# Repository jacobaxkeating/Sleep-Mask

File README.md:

# Circadian Sleep Mask

## Overview
A battery powered sleep mask that gradually illuminates the inside of the mask as the user's alarm approaches. The user sets their sleep duration by pressing a button on the housing, and the device begins lighting up that many hours later. Waking this way is closer to how the body wakes naturally, easing the user out of sleep rather than jolting them awake. It reduces sleep inertia, the grogginess and disorientation that follows an abrupt alarm

[Schematic (PDF)](outputs/schematic/sleep_mask.pdf)

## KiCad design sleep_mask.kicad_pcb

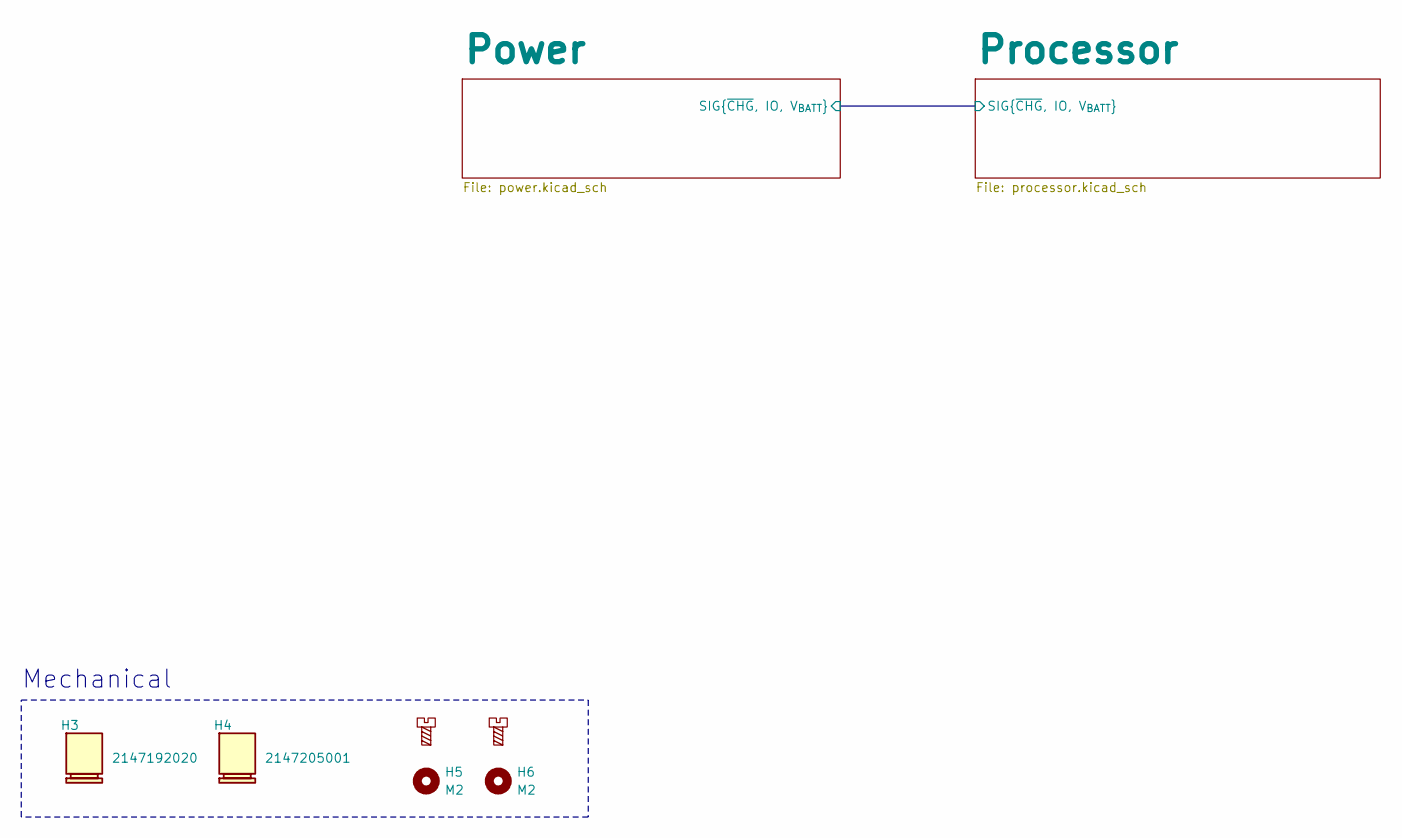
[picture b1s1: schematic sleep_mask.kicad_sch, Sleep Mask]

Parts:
H1, H2: MountingScrew
H3: 2147192020; Manufacturer_Part_Number 2147192020
H4: 2147205001; Manufacturer_Part_Number 2147205001
H5, H6: M2; MountingHole_2.2mm_M2

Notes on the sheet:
Mechanical

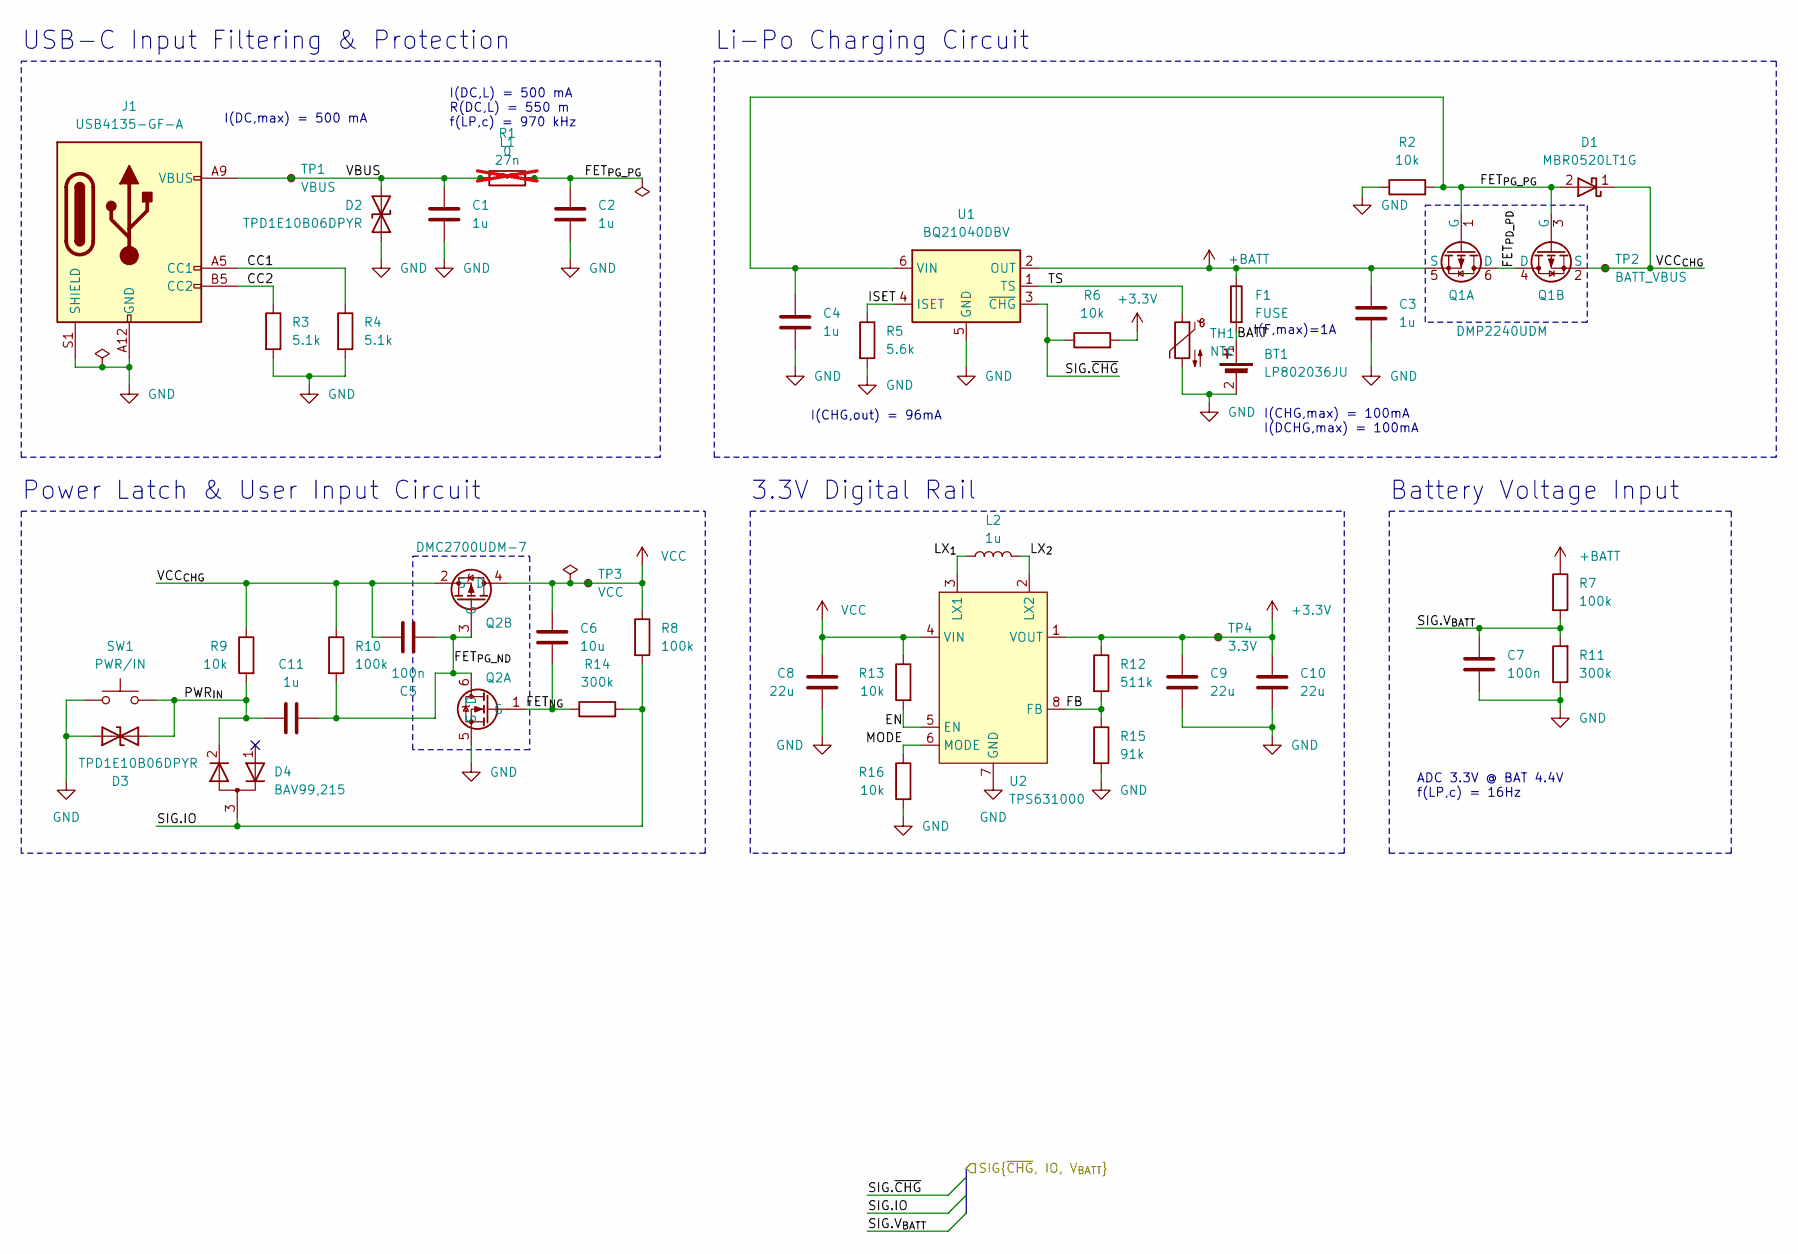
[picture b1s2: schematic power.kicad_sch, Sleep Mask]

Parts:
BT1: LP802036JU; R_1206_3216Metric_Pad1.30x1.75mm_HandSolder; Manufacturer_Part_Number LP802036JU +PCM+2IC+2 WIRES 50MM
C1, C2, C3, C4, C11: 1u; C_0402_1005Metric; Manufacturer_Part_Number CL05A105KO5NNNC
C5, C7: 100n; C_0402_1005Metric; Manufacturer_Part_Number CL05B104KO5NNNC
C6: 10u; C_0603_1608Metric; Manufacturer_Part_Number CL10X106MO8NRNC
C8, C9, C10: 22u; C_0805_2012Metric; Manufacturer_Part_Number CL21A226MAYNNNE
D1: MBR0520LT1G; D_SOD-123; Manufacturer_Part_Number MBR0520LT1G
D2, D3: TPD1E10B06DPYR; Texas_DPY0002A_0.6x1mm_P0.65mm; Manufacturer_Part_Number TPD1E10B06DPYR
D4: BAV99,215; TSOT-23; Manufacturer_Part_Number BAV99,215
F1: FUSE; R_0603_1608Metric; Manufacturer_Part_Number MFU0603FF01000P500
J1: USB4135-GF-A; USB_C_Receptacle_GCT_USB4135-GF-A_6P_TopMnt_Horizontal; Manufacturer_Part_Number USB4135-GF-A
L1: 27n; L_0603_1608Metric; Manufacturer_Part_Number LQG18HN27NJ00D; not fitted
L2: 1u; L_0603_1608Metric; Manufacturer_Part_Number DFE18SAN1R0MG0L
Q1: DMP2240UDM; SOT-23-6; Manufacturer_Part_Number DMP2240UDM
Q2: DMC2700UDM-7; SOT-23-6; Manufacturer_Part_Number DMC2700UDM-7
R1: 0; R_0603_1608Metric; Manufacturer_Part_Number RC0603JR-070RL
R2, R6, R9, R13, R16: 10k; R_0603_1608Metric; Manufacturer_Part_Number RK73H1JTTD1002F
R3, R4: 5.1k; R_0603_1608Metric; Manufacturer_Part_Number RK73H1JTTD5101F
R5: 5.6k; R_0603_1608Metric; Manufacturer_Part_Number RC0603FR-075K6L
R7, R8, R10: 100k; R_0603_1608Metric; Manufacturer_Part_Number RK73H1JTTD1003F
R11, R14: 300k; R_0603_1608Metric; Manufacturer_Part_Number RK73H1JTTD3003F
R12: 511k; R_0603_1608Metric; Manufacturer_Part_Number RK73H1JTTD5113F
R15: 91k; R_0603_1608Metric; Manufacturer_Part_Number RC0603FR-0791KL
SW1: PWR/IN; SW_Push_1P1T-MP_NO_Horizontal_Alps_SKRTLAE010; Manufacturer_Part_Number SKRTLAE010
TH1: NTC; R_0402_1005Metric; Manufacturer_Part_Number NTCG103JF103FT1
TP1: VBUS; TestPoint_Pad_D1.0mm
TP2: BATT_VBUS; TestPoint_Pad_D1.0mm
TP3: VCC; TestPoint_Pad_D1.0mm
TP4: 3.3V; TestPoint_Pad_D1.0mm
U1: BQ21040DBV; SOT-23-6; Manufacturer_Part_Number BQ21040DBVT
U2: TPS631000; SOT-583-8; Manufacturer_Part_Number TPS631000DRLR

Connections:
+3.3V: C9.2, C10.2, R6.2, R12.1, TP4.1, U2.1 (VOUT); also elsewhere on the board
+BATT: C3.1, F1.1, Q1.5 (S), R7.1, U1.2 (OUT)
/Power/BATT: BT1.1 (+), F1.2
/Power/CC1: J1.A5 (CC1), R4.1
/Power/CC2: J1.B5 (CC2), R3.1
/Power/EN: R13.2, U2.5 (EN)
/Power/FB: R12.2, R15.1, U2.8 (FB)
/Power/FET_{NG}: C6.2, Q2.1 (G), R14.1
/Power/FET_{PD_PD}: Q1.4 (D), Q1.6 (D)
/Power/FET_{PG_ND}: C5.2, C11.2, Q2.3 (G), Q2.6 (D), R10.2
/Power/FET_{PG_PG}: C2.1, C4.1, D1.2 (A), L1.2, Q1.1 (G), Q1.3 (G), R1.2, R2.2, U1.6 (VIN)
/Power/ISET: R5.1, U1.4 (ISET)
/Power/LX_{1}: L2.1, U2.3 (LX1)
/Power/LX_{2}: L2.2, U2.2 (LX2)
/Power/MODE: R16.1, U2.6 (MODE)
/Power/PWR_{IN}: C11.1, D3.2 (A2), D4.2 (K), R9.2, SW1.2
/Power/SIG.IO: D4.3 (common), R8.2, R14.2; also elsewhere on the board
/Power/SIG.V_{BATT}: C7.1, R7.2, R11.2; also elsewhere on the board
/Power/SIG.~CHG: R6.1, U1.3 (~CHG); also elsewhere on the board
/Power/TS: TH1.1, U1.1 (TS)
/Power/VBUS: C1.1, D2.2 (A2), J1.A9 (VBUS), J1.B9 (VBUS), L1.1, R1.1, TP1.1
/Power/VCC_{CHG}: C5.1, D1.1 (K), Q1.2 (S), Q2.2 (S), R9.1, R10.1, TP2.1
GND: BT1.2 (-), C1.2, C2.2, C3.2, C4.2, C7.2, C8.1, C9.1, C10.1, D2.1 (A1), D3.1 (A1), J1.A12 (GND), J1.B12 (GND), J1.S1 (SHIELD), Q2.5 (S), R2.1, R3.2, R4.2, R5.2, R11.1, R15.2, R16.2, SW1.1, TH1.2, U1.5 (GND), U2.7 (GND); also elsewhere on the board
VCC: C6.1, C8.2, Q2.4 (D), R8.1, R13.1, TP3.1, U2.4 (VIN); also elsewhere on the board

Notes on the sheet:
I(F,max)=1A
I(CHG,out) = 96mA
I(DC,max) = 500 mA
I(DC,L) = 500 mA R(DC,L) = 550 m f(LP,c) = 970 kHz
I(CHG,max) = 100mA I(DCHG,max) = 100mA
3.3V Digital Rail
Li-Po Charging Circuit
USB-C Input Filtering & Protection
Battery Voltage Input
Power Latch & User Input Circuit
ADC 3.3V @ BAT 4.4V f(LP,c) = 16Hz

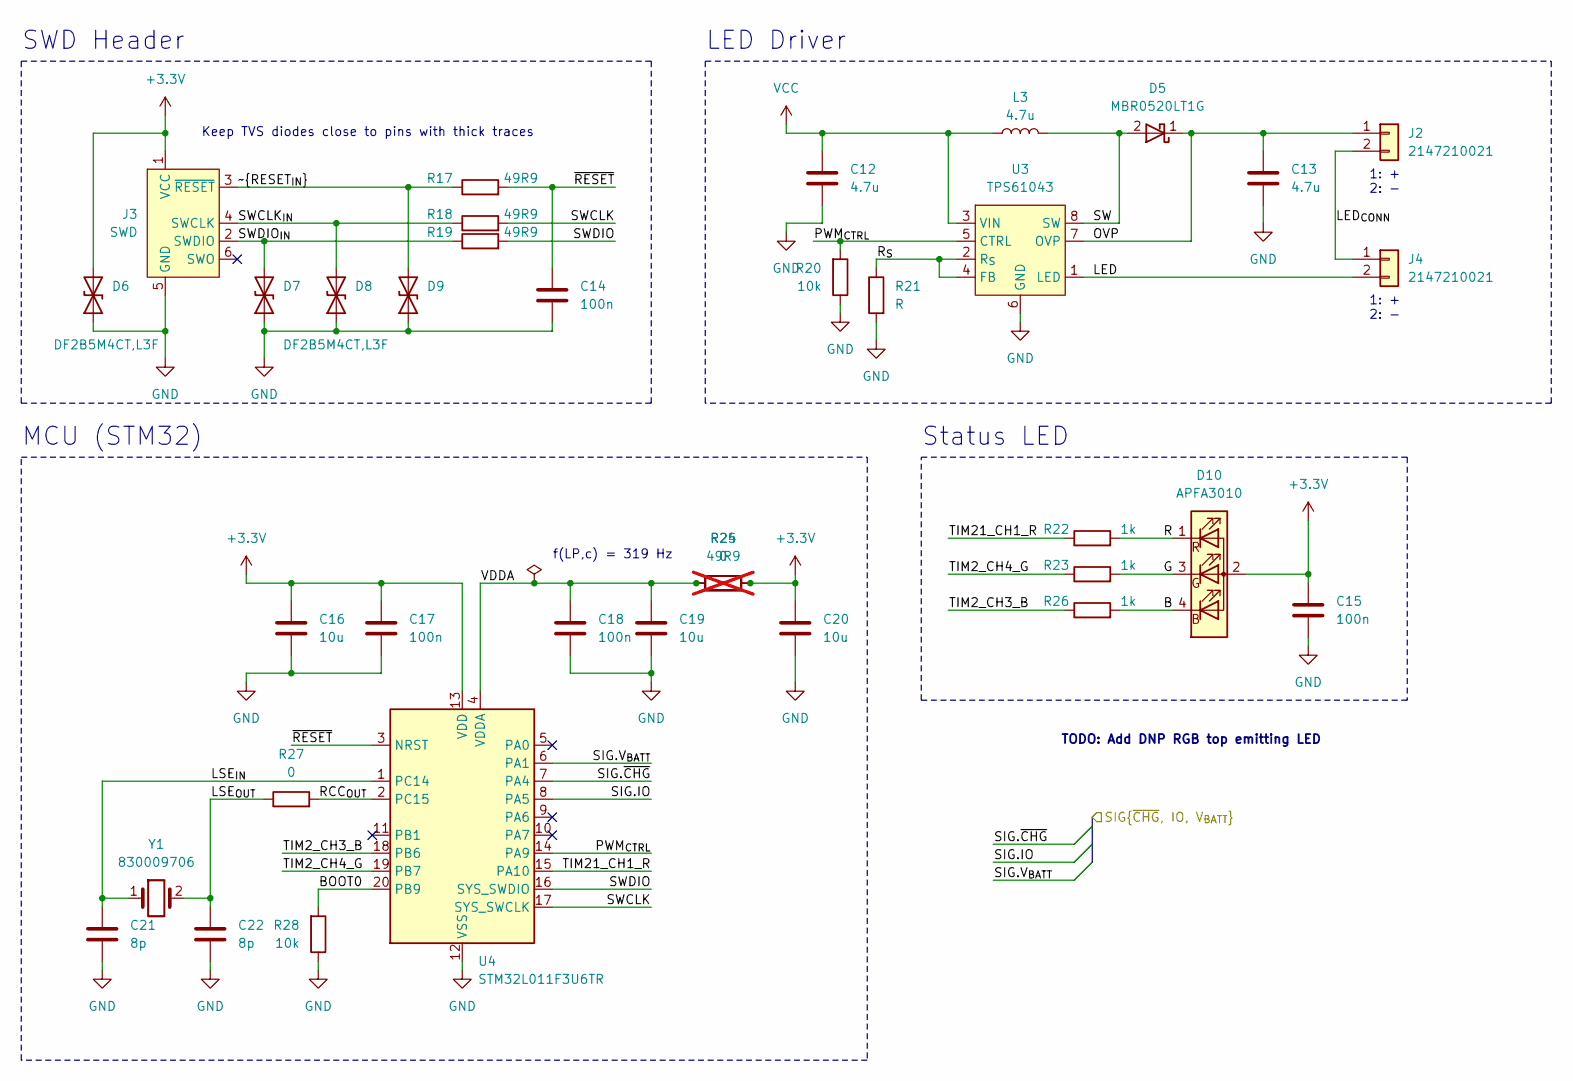
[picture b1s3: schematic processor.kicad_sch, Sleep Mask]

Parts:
C12, C13: 4.7u; C_0603_1608Metric; Manufacturer_Part_Number GRM188R6YA475KE15D
C14, C15, C17, C18: 100n; C_0402_1005Metric; Manufacturer_Part_Number CL05B104KO5NNNC
C16, C19, C20: 10u; C_0603_1608Metric; Manufacturer_Part_Number CL10X106MO8NRNC
C21, C22: 8p; C_0402_1005Metric; Manufacturer_Part_Number CL05C080DB51PNC
D5: MBR0520LT1G; D_SOD-123; Manufacturer_Part_Number MBR0520LT1G
D6, D7, D8, D9: DF2B5M4CT,L3F; D_SOD-882; Manufacturer_Part_Number DF2B5M4CT,L3F
D10: APFA3010; LED_Kingbright_APFA3010_3x1.5mm_Horizontal; Manufacturer_Part_Number APFA3010LSEEZGKQBKC
J2, J4: 2147210021; Manufacturer_Part_Number 2147210021
J3: SWD; Tag-Connect_TC2030-IDC-NL_2x03_P1.27mm_Vertical
L3: 4.7u; L_0805_2012Metric; Manufacturer_Part_Number MLZ2012N4R7LT000
R17, R18, R19: 49R9; R_0603_1608Metric; Manufacturer_Part_Number RC0603FR-0749R9L
R20, R28: 10k; R_0603_1608Metric; Manufacturer_Part_Number RK73H1JTTD1002F
R21: R; R_0603_1608Metric
R22, R23, R26: 1k; R_0603_1608Metric; Manufacturer_Part_Number RK73H1JTTD1001F
R24: 49R9; R_0603_1608Metric; Manufacturer_Part_Number RC0603FR-0749R9L; not fitted
R25, R27: 0; R_0603_1608Metric; Manufacturer_Part_Number RC0603JR-070RL
U3: TPS61043; Texas_DRB0008A; Manufacturer_Part_Number TPS61043DRBR
U4: STM32L011F3U6TR; ST_UFQFPN-20_3x3mm_P0.5mm; Manufacturer_Part_Number STM32L011F3U6TR
Y1: 830009706; Crystal_SMD_G8-2Pin_3.2x1.5mm; MPN ABS05-32.768KHZ-9-T

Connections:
+3.3V: C15.2, C16.1, C17.1, C20.1, D6.2 (A2), D10.2 (A), J3.1 (VCC), R24.2, R25.2, U4.13 (VDD); also elsewhere on the board
/Power/SIG.IO: U4.8 (PA5); also elsewhere on the board
/Power/SIG.V_{BATT}: U4.6 (PA1); also elsewhere on the board
/Power/SIG.~CHG: U4.7 (PA4); also elsewhere on the board
/Processor/B: D10.4 (B), R26.2
/Processor/BOOT0: R28.2, U4.20 (PB9)
/Processor/G: D10.3 (G), R23.2
/Processor/LED: J4.2, U3.1 (LED)
/Processor/LED_{CONN}: J2.2, J4.1
/Processor/LSE_{IN}: C21.1, U4.1 (PC14), Y1.1
/Processor/LSE_{OUT}: C22.1, R27.1, Y1.2
/Processor/OVP: C13.2, D5.1 (K), J2.1, U3.7 (OVP)
/Processor/PWM_{CTRL}: R20.2, U3.5 (CTRL), U4.14 (PA9)
/Processor/R: D10.1 (R), R22.2
/Processor/RCC_{OUT}: R27.2, U4.2 (PC15)
/Processor/R_{S}: R21.1, U3.2 (R_{S}), U3.4 (FB)
/Processor/SW: D5.2 (A), L3.2, U3.8 (SW)
/Processor/SWCLK: R18.2, U4.17 (SYS_SWCLK)
/Processor/SWCLK_{IN}: D8.2 (A2), J3.4 (SWCLK), R18.1
/Processor/SWDIO: R19.2, U4.16 (SYS_SWDIO)
/Processor/SWDIO_{IN}: D7.2 (A2), J3.2 (SWDIO), R19.1
/Processor/TIM2_CH3_B: R26.1, U4.18 (PB6)
/Processor/TIM2_CH4_G: R23.1, U4.19 (PB7)
/Processor/TIM21_CH1_R: R22.1, U4.15 (PA10)
/Processor/VDDA: C18.1, C19.1, R24.1, R25.1, U4.4 (VDDA)
/Processor/~RESET_{IN}: D9.2 (A2), J3.3 (~RESET), R17.1
/Processor/~RESET: C14.2, R17.2, U4.3 (NRST)
GND: C12.1, C13.1, C14.1, C15.1, C16.2, C17.2, C18.2, C19.2, C20.2, C21.2, C22.2, D6.1 (A1), D7.1 (A1), D8.1 (A1), D9.1 (A1), J3.5 (GND), R20.1, R21.2, R28.1, U3.6 (GND), U3.9 (TP), U4.12 (VSS); also elsewhere on the board
VCC: C12.2, L3.1, U3.3 (VIN); also elsewhere on the board

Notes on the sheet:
Keep TVS diodes close to pins with thick traces
SWD Header
TODO: Add DNP RGB top emitting LED
1: + 2: -
LED Driver
f(LP,c) = 319 Hz
MCU (STM32)
Status LED

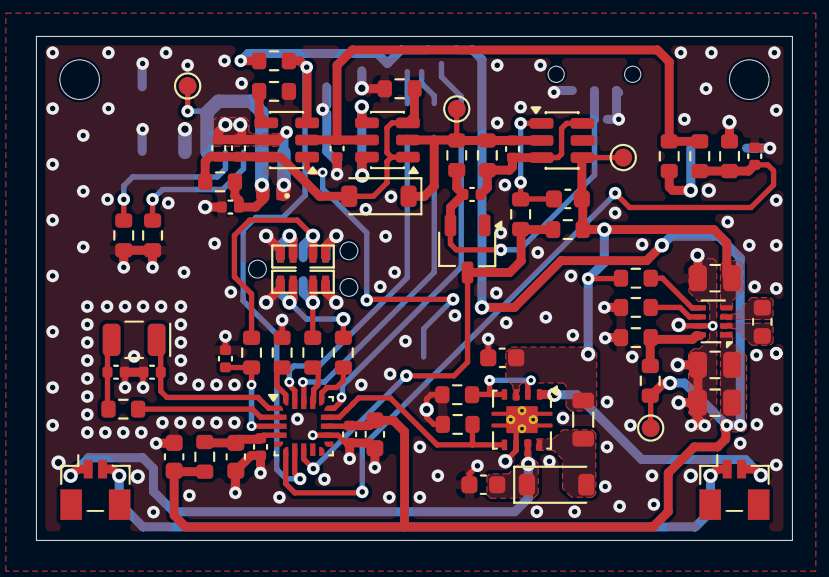
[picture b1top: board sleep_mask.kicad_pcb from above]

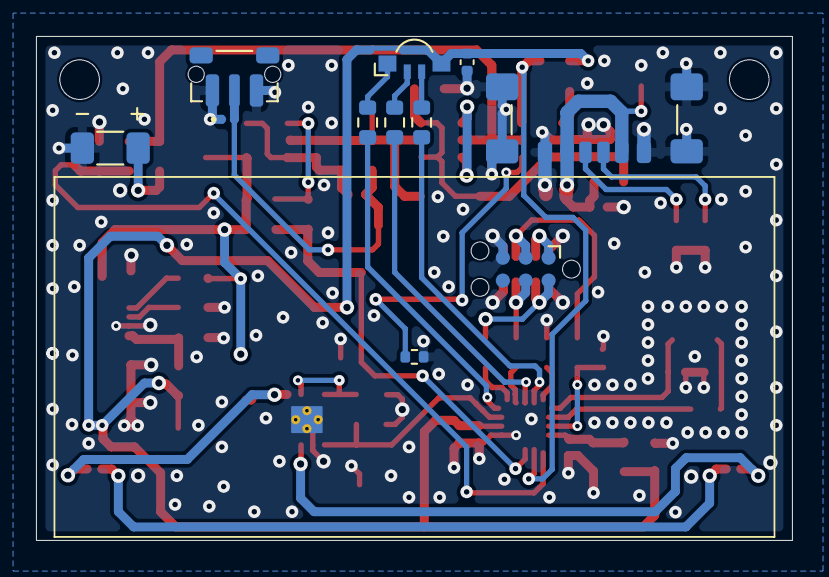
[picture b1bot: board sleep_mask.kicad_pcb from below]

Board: 4 copper layers, 42.0 x 28.0 mm, 82 parts (11 on the bottom side), 47 nets.

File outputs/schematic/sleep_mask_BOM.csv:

"Reference","Value","Qty","MPN1","Manufacturer1","Footprint","Datasheet","COO","DNP","Description","MPN2","Manufacturer2"
"BT1","LP802036JU","1","","","Resistor_SMD:R_1206_3216Metric_Pad1.30x1.75mm_HandSolder","https://www.jauch.com/downloadfile/5ef1edcfd8b3ac6cf0afebf9d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","","","BATTERY 3.7V 500MAH","",""
"C1,C2,C3,C4,C11,L2","1u","6","","","Capacitor_SMD:C_0402_1005Metric,Inductor_SMD:L_0603_1608Metric","https://mm.digikey.com/Volume0/opasdata/d220001/medias/docus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,https://search.murata.co.jp/Ceramy/image/img/P02/JETE243A-0036.pdf","","","CAP CER 1UF 16V X5R 0402,FIXED IND 1UH 1.7A 128 MOHM SMD","",""
"C5,C7,C14,C15,C17,C18","100n","6","","","Capacitor_SMD:C_0402_1005Metric","https://mm.digikey.com/Volume0/opasdata/d220001/medias/docus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","","","CAP CER 0.1UF 16V X7R 0402","",""
"C6,C16,C19,C20","10u","4","","","Capacitor_SMD:C_0603_1608Metric","https://mm.digikey.com/Volume0/opasdata/d220001/medias/docus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","","","CAP CER 10UF 16V X6S 0603","",""
"C8,C9,C10","22u","3","","","Capacitor_SMD:C_0805_2012Metric","https://mm.digikey.com/Volume0/opasdata/d220001/medias/docus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","","","CAP CER 22UF 25V X5R 0805","",""
"C12,C13,L3","4.7u","3","","","Capacitor_SMD:C_0603_1608Metric,Inductor_SMD:L_0805_2012Metric","https://product.tdk.com/en/system/files?file=dam/doc/product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,https://search.murata.co.jp/Ceramy/image/img/A01X/G101/ENG/G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","","","CAP CER 4.7UF 35V X5R 0603,FIXED IND 4.7UH 600MA 180 MOHM","",""
"C21,C22","8p","2","","","Capacitor_SMD:C_0402_1005Metric","https://mm.digikey.com/Volume0/opasdata/d220001/medias/docus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","","","CAP CER 8PF 50V C0G/NP0 0402","",""
"D1,D5","MBR0520LT1G","2","","","Diode_SMD:D_SOD-123","https://www.onsemi.com/pdf/datasheet/mbr0520lt1-d.pdf","","","DIODE SCHOTTKY 20V 500MA SOD123","",""
"D2,D3","TPD1E10B06DPYR","2","","","Package_SON:Texas_DPY0002A_0.6x1mm_P0.65mm","https://www.ti.com/general/docs/suppproductinfo.tsp?distId=1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","","","TVS DIODE 5.5VWM 14VC 2X1SON","",""
"D4","BAV99,215","1","","","Package_TO_SOT_SMD:TSOT-23","https://assets.nexperia.com/documents/data-sheet/BAV99.pdf","","","DIODE ARR GP 100V 215MA TO-236AB","",""
"D6,D7,D8,D9","DF2B5M4CT,L3F","4","","","Diode_SMD:D_SOD-882","https://toshiba.semicon-storage.com/info/docget.jsp?did=5577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","","","TVS DIODE 3.6VWM 15VC CST2","",""
"D10","APFA3010","1","","","LED_SMD:LED_Kingbright_APFA3010_3x1.5mm_Horizontal","https://www.KingbrightUSA.com/images/catalog/SPEC/APFA3010LS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","","","LED RGB CLEAR 4SMD R/A","",""
"F1","FUSE","1","","","Resistor_SMD:R_0603_1608Metric","https://www.vishay.com/docs/28747/mfuserie.pdf","","","FUSE BOARD MOUNT 1A 32VDC 0603","",""
"H3","2147192020","1","","","","https://www.molex.com/en-us/products/part-detail/2147192020?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","","","CONN HDR HSG 2POS 0.80MM","",""
"H4","2147205001","1","","","","https://www.molex.com/pdm_docs/sd/2147205001_sd.pdf","","","ZERO-HACHI 0.8 CRIMP TERM #30-32","",""
"J1","USB4135-GF-A","1","","","Connector_USB:USB_C_Receptacle_GCT_USB4135-GF-A_6P_TopMnt_Horizontal","https://gct.co/files/specs/usb4135-spec.pdf","","","USB C REC GF RA 6P SMT & SMT SHE","",""
"J2,J4","2147210021","2","","","sleep_mask:2147210021","https://www.molex.com/en-us/products/part-detail/2147210021?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","","","ZERO-HACHI 0.8 HDR SR RA ETP AU","",""
"L1","27n","1","","","Inductor_SMD:L_0603_1608Metric","https://search.murata.co.jp/Ceramy/image/img/P02/JELF243B-0002.pdf","","DNP","FIXED IND 27NH 500MA 550 MOHM","",""
"Q1","DMP2240UDM","1","","","Package_TO_SOT_SMD:SOT-23-6","https://www.diodes.com/assets/Datasheets/ds31197.pdf","","","MOSFET 2P-CH 20V 2A SOT26","",""
"Q2","DMC2700UDM-7","1","","","Package_TO_SOT_SMD:SOT-23-6","https://www.diodes.com/assets/Datasheets/DMC2700UDM.pdf","","","MOSFET N/P-CH 20V 1.34A SOT26","",""
"R1,R25,R27","0","3","","","Resistor_SMD:R_0603_1608Metric","https://yageogroup.com/content/datasheet/asset/file/PYU-RC_G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","","","RES 0 OHM JUMPER 1/10W 0603","",""
"R2,R6,R9,R13,R16,R20,R28","10k","7","","","Resistor_SMD:R_0603_1608Metric","https://www.koaspeer.com/pdfs/RK73H.pdf","","","RES 10K OHM 1% 1/10W 0603","",""
"R3,R4","5.1k","2","","","Resistor_SMD:R_0603_1608Metric","https://www.koaspeer.com/pdfs/RK73H.pdf","","","RES 5.1K OHM 1% 1/10W 0603","",""
"R5","5.6k","1","","","Resistor_SMD:R_0603_1608Metric","https://yageogroup.com/content/datasheet/asset/file/PYU-RC_G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","","","RES 5.6K OHM 1% 1/10W 0603","",""
"R7,R8,R10","100k","3","","","Resistor_SMD:R_0603_1608Metric","https://www.koaspeer.com/pdfs/RK73H.pdf","","","RES 100K OHM 1% 1/10W 0603","",""
"R11,R14","300k","2","","","Resistor_SMD:R_0603_1608Metric","https://www.koaspeer.com/pdfs/RK73H.pdf","","","RES 300K OHM 1% 1/10W 0603","",""
"R12","511k","1","","","Resistor_SMD:R_0603_1608Metric","https://www.koaspeer.com/pdfs/RK73H.pdf","","","RES 511K OHM 1% 1/10W 0603","",""
"R15","91k","1","","","Resistor_SMD:R_0603_1608Metric","https://yageogroup.com/content/datasheet/asset/file/PYU-RC_G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","","","RES 91K OHM 1% 1/10W 0603","",""
"R17,R18,R19","49R9","3","","","Resistor_SMD:R_0603_1608Metric","https://yageogroup.com/content/datasheet/asset/file/PYU-RC_G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","","","RES 49.9 OHM 1% 1/10W 0603","",""
"R21","R","1","","","Resistor_SMD:R_0603_1608Metric","","","","~","",""
"R22,R23,R26","1k","3","","","Resistor_SMD:R_0603_1608Metric","https://www.koaspeer.com/pdfs/RK73H.pdf","","","RES 1K OHM 1% 1/8W 0603","",""
"R24","49R9","1","","","Resistor_SMD:R_0603_1608Metric","https://yageogroup.com/content/datasheet/asset/file/PYU-RC_G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","","DNP","RES 49.9 OHM 1% 1/10W 0603","",""
"SW1","PWR/IN","1","","","Button_Switch_SMD:SW_Push_1P1T-MP_NO_Horizontal_Alps_SKRTLAE010","https://tech.alpsalpine.com/cms.media/product_spec_skrtlae01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","","","SWITCH TACTILE SPST-NO 0.05A 12V","",""
"TH1","NTC","1","","","Resistor_SMD:R_0402_1005Metric","https://product.tdk.com/system/files/dam/doc/product/sensor/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","","","THERMISTOR NTC 10KOHM 3380K 0402","",""
"TP1","VBUS","1","","","TestPoint:TestPoint_Pad_D1.0mm","","","","~","",""
"TP2","BATT_VBUS","1","","","TestPoint:TestPoint_Pad_D1.0mm","","","","~","",""
"TP3","VCC","1","","","TestPoint:TestPoint_Pad_D1.0mm","","","","~","",""
"TP4","3.3V","1","","","TestPoint:TestPoint_Pad_D1.0mm","","","","~","",""
"U1","BQ21040DBV","1","","","Package_TO_SOT_SMD:SOT-23-6","https://www.ti.com/general/docs/suppproductinfo.tsp?distId=1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","","","IC BATT CHG LI-ION 1CELL SOT23-6","",""
"U2","TPS631000","1","","","Package_TO_SOT_SMD:SOT-583-8","https://www.ti.com/lit/ds/symlink/tps631000.pdf","","","IC REG BUCK BOOST ADJ 2A SOT-583","",""
"U3","TPS61043","1","","","Package_DFN_QFN:Texas_DRB0008A","https://www.ti.com/lit/ds/slvs465c/slvs465c.pdf","","","IC LED DRVR RGLTR PWM 60MA 8SON","",""
"U4","STM32L011F3U6TR","1","","","Package_DFN_QFN:ST_UFQFPN-20_3x3mm_P0.5mm","https://www.st.com/resource/en/datasheet/stm32l011f3.pdf","","","IC MCU 32BIT 8KB FLASH 20UFQFPN","",""
"Y1","830009706","1","","","Crystal:Crystal_SMD_G8-2Pin_3.2x1.5mm","https://www.we-online.com/components/products/datasheet/8300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","","","CRYSTAL 32.7680KHZ 9PF SMD","",""
